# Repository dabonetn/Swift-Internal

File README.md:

# Swift-Internal
Internal Swiftlink Wifi Modems for 64 Breadbins and C128.

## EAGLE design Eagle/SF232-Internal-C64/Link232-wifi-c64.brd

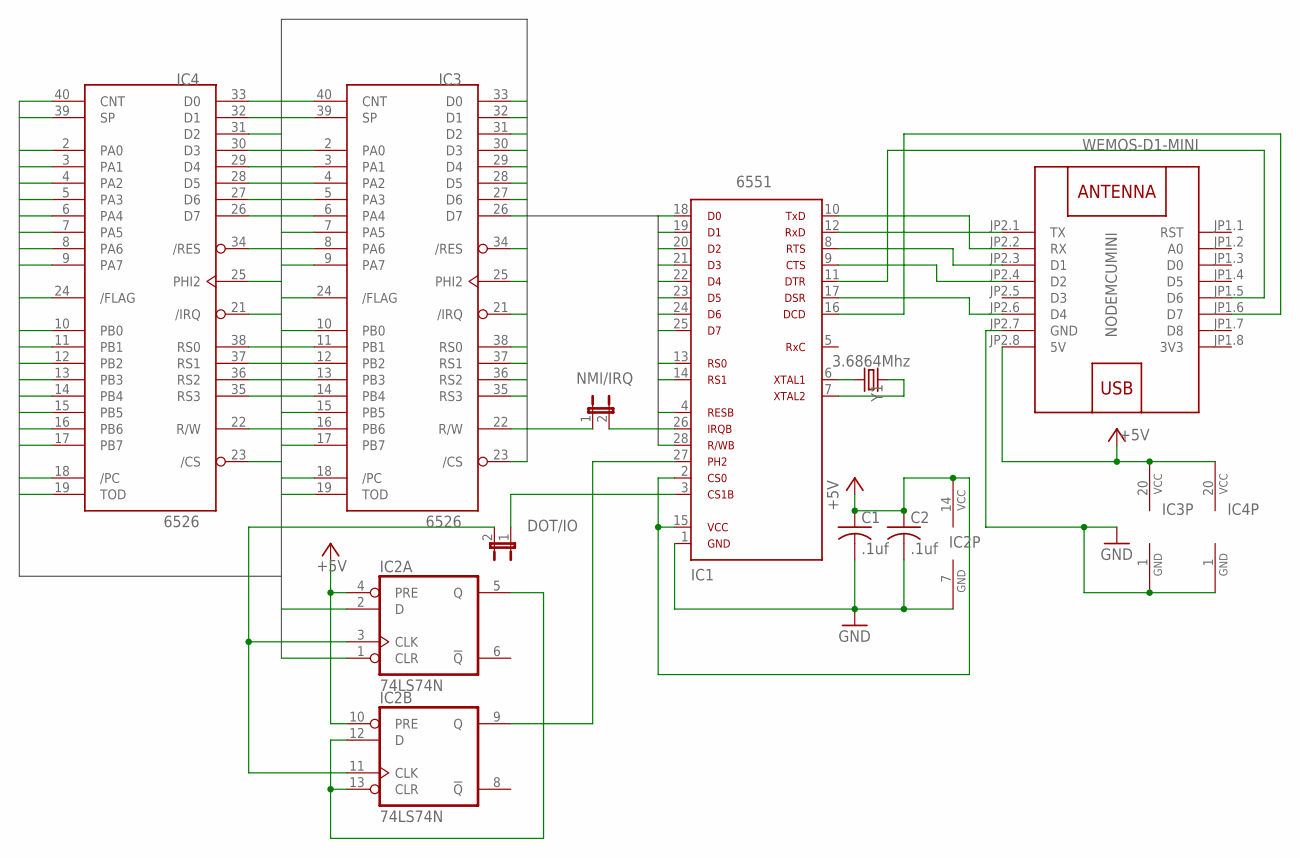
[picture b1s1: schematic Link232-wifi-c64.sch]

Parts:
C1, C2: .1uf; C050-024X044
IC1: 6551
IC2: 74LS74N; DIL14
IC3, IC4: 6526; DIP40
JP1: NMI/IRQ; JP1
JP2: DOT/IO; JP1
NODEMCUMINI: WEMOS-D1-MINI
Y1: 3.6864Mhz; HC49US

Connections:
3V3: NODEMCUMINI.JP1.8 (3V3)
+5V: C1.1, C2.1, IC1.2, IC1.15, IC2.4 (PRE), IC2.10 (PRE), IC2.14 (VCC), IC3.20 (VCC), IC4.20 (VCC), NODEMCUMINI.JP2.8 (5V)
/CS: IC3.23 (/CS), IC4.23 (/CS)
/FLAG: IC3.24 (/FLAG), IC4.24 (/FLAG)
/PC: IC3.18 (/PC), IC4.18 (/PC)
CNT: IC3.40 (CNT), IC4.40 (CNT)
D0: IC1.18, IC3.33 (D0), IC4.33 (D0)
D1: IC1.19, IC3.32 (D1), IC4.32 (D1)
D2: IC1.20, IC3.31 (D2), IC4.31 (D2)
D3: IC1.21, IC3.30 (D3), IC4.30 (D3)
D4: IC1.22, IC3.29 (D4), IC4.29 (D4)
D5: IC1.23, IC3.28 (D5), IC4.28 (D5)
D6: IC1.24, IC3.27 (D6), IC4.27 (D6)
D7: IC1.25, IC3.26 (D7), IC4.26 (D7)
GND: C1.2, C2.2, IC1.1, IC2.7 (GND), IC3.1 (GND), IC4.1 (GND), NODEMCUMINI.JP2.7 (GND)
IRQ: IC3.21 (/IRQ), IC4.21 (/IRQ), JP1.1
unnamed: IC2.3 (CLK), IC2.11 (CLK), JP2.2
unnamed: IC2.5 (Q), IC2.12 (D), IC2.13 (CLR)
unnamed: IC1.27, IC2.9 (Q)
unnamed: IC1.26, JP1.2
unnamed: IC1.3, JP2.1
unnamed: IC1.6, Y1.2
unnamed: IC1.7, Y1.1
unnamed: IC1.12, NODEMCUMINI.JP2.1 (TX)
unnamed: IC1.10, NODEMCUMINI.JP2.2 (RX)
unnamed: IC1.8, NODEMCUMINI.JP2.3 (D1)
unnamed: IC1.9, NODEMCUMINI.JP2.4 (D2)
unnamed: IC1.17, NODEMCUMINI.JP2.6 (D4)
unnamed: IC1.11, NODEMCUMINI.JP1.5 (D6)
unnamed: IC1.16, NODEMCUMINI.JP1.6 (D7)
PA0: IC3.2 (PA0), IC4.2 (PA0)
PA1: IC3.3 (PA1), IC4.3 (PA1)
PA2: IC3.4 (PA2), IC4.4 (PA2)
PA3: IC3.5 (PA3), IC4.5 (PA3)
PA4: IC3.6 (PA4), IC4.6 (PA4)
PA5: IC3.7 (PA5), IC4.7 (PA5)
PA6: IC3.8 (PA6), IC4.8 (PA6)
PA7: IC3.9 (PA7), IC4.9 (PA7)
PB0: IC3.10 (PB0), IC4.10 (PB0)
PB1: IC3.11 (PB1), IC4.11 (PB1)
PB2: IC3.12 (PB2), IC4.12 (PB2)
PB3: IC3.13 (PB3), IC4.13 (PB3)
PB4: IC3.14 (PB4), IC4.14 (PB4)
PB5: IC3.15 (PB5), IC4.15 (PB5)
PB6: IC3.16 (PB6), IC4.16 (PB6)
PB7: IC3.17 (PB7), IC4.17 (PB7)
PHI2: IC2.1 (CLR), IC2.2 (D), IC3.25 (PHI2), IC4.25 (PHI2)
RES: IC1.4, IC3.34 (/RES), IC4.34 (/RES)
RS0: IC1.13, IC3.38 (RS0), IC4.38 (RS0)
RS1: IC1.14, IC3.37 (RS1), IC4.37 (RS1)
RS2: IC3.36 (RS2), IC4.36 (RS2)
RS3: IC3.35 (RS3), IC4.35 (RS3)
RW: IC1.28, IC3.22 (R/W), IC4.22 (R/W)
SP: IC3.39 (SP), IC4.39 (SP)
TOD: IC3.19 (TOD), IC4.19 (TOD)

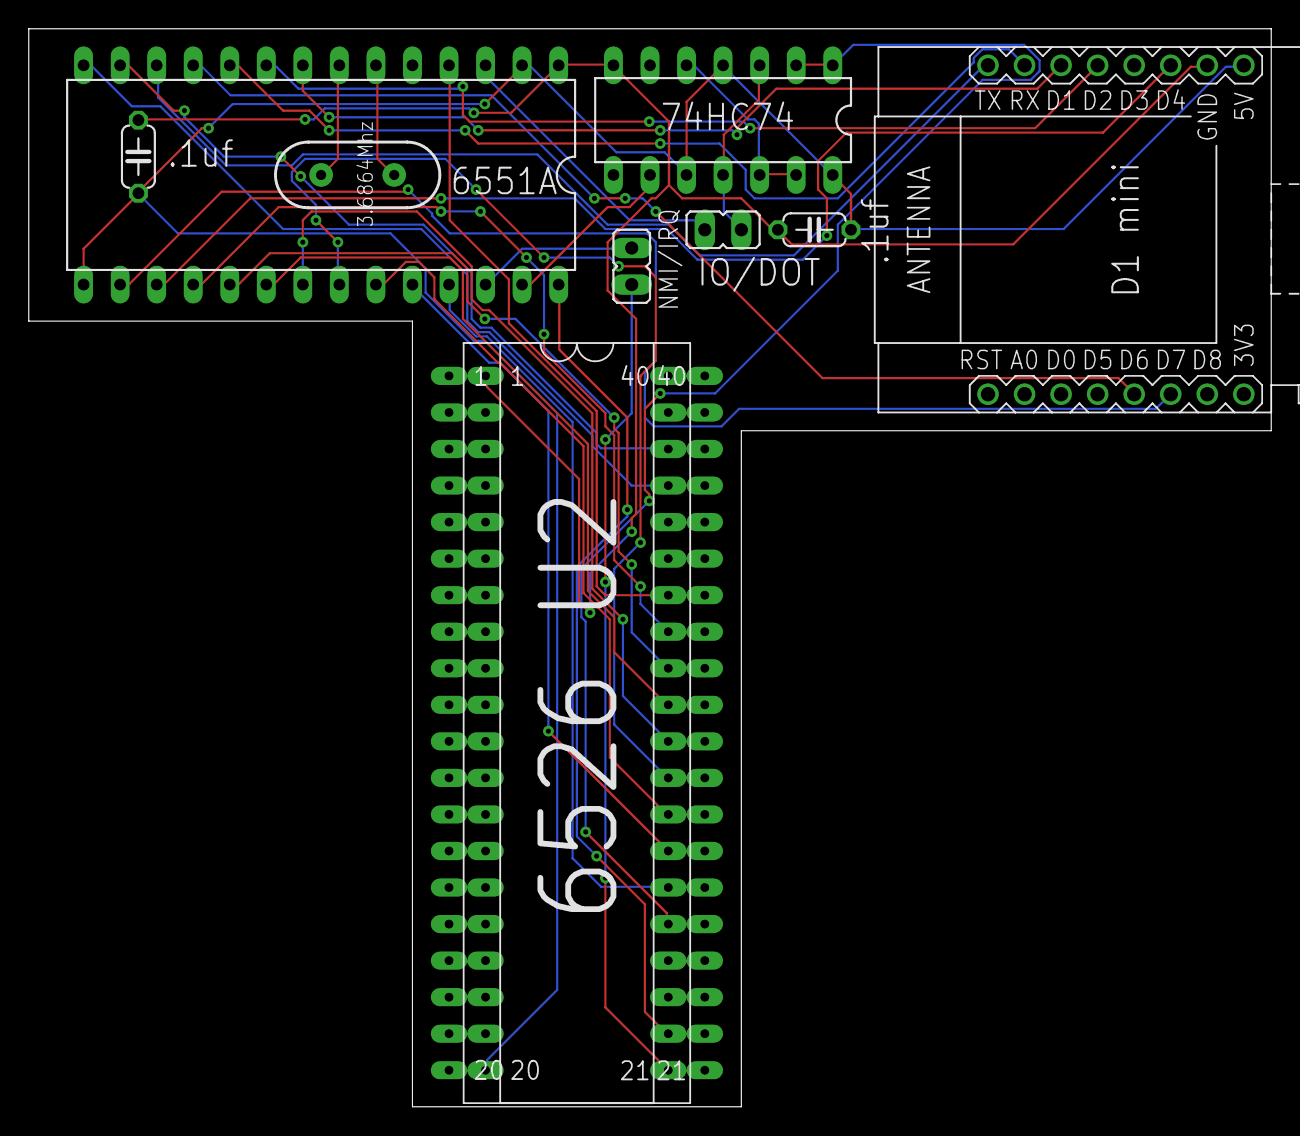
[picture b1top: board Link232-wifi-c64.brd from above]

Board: 2 copper layers, 86.4 x 74.9 mm, 10 parts (0 on the bottom side), 54 nets.

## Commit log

2020-07-10 Inital Commit.
    Inital Commit.
2020-08-12 Added install guides
2020-08-12 Update and bugfix for zimodem
    Fixed DCD not raising on manual answer. Fixed NO CARRIER being cut off to NO.
2021-01-02 Update to Zimodem 3.5.6 Base
2021-01-02 Update Readme.
2021-11-07 Update readme.txt
    Removed tindie.
2022-03-29 Updated documentation.
    Updated documentation.
2022-05-11 Board revision 1.3 Added

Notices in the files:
parts and their libraries:
diy-modules: Released under the Creative Commons Attribution 4.0 International License: http://creativecommons.org/licenses/by/4.0
SparkFun-Clocks: Licensing: Creative Commons ShareAlike 4.0 International - https://creativecommons.org/licenses/by-sa/4.0
